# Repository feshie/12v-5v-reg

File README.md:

12v-5v-reg
==========

A switched 12Volt to 5Volt regulator

Will take a nominal 12v in (designed for a lead acid) and produced a regulated 5v supply capable of supplying 2A.

The onboard LEDs show the prescenec of 12V, the switch status, and the prescence of the 5V output.  These LEDs can be disabled to minimise power usage

There is a bypass jumper to enable the output to remain active independently of the enable status.

The enable pins will turn the output on high.

This board has yet to be built and tested so should be considered in alpha status.

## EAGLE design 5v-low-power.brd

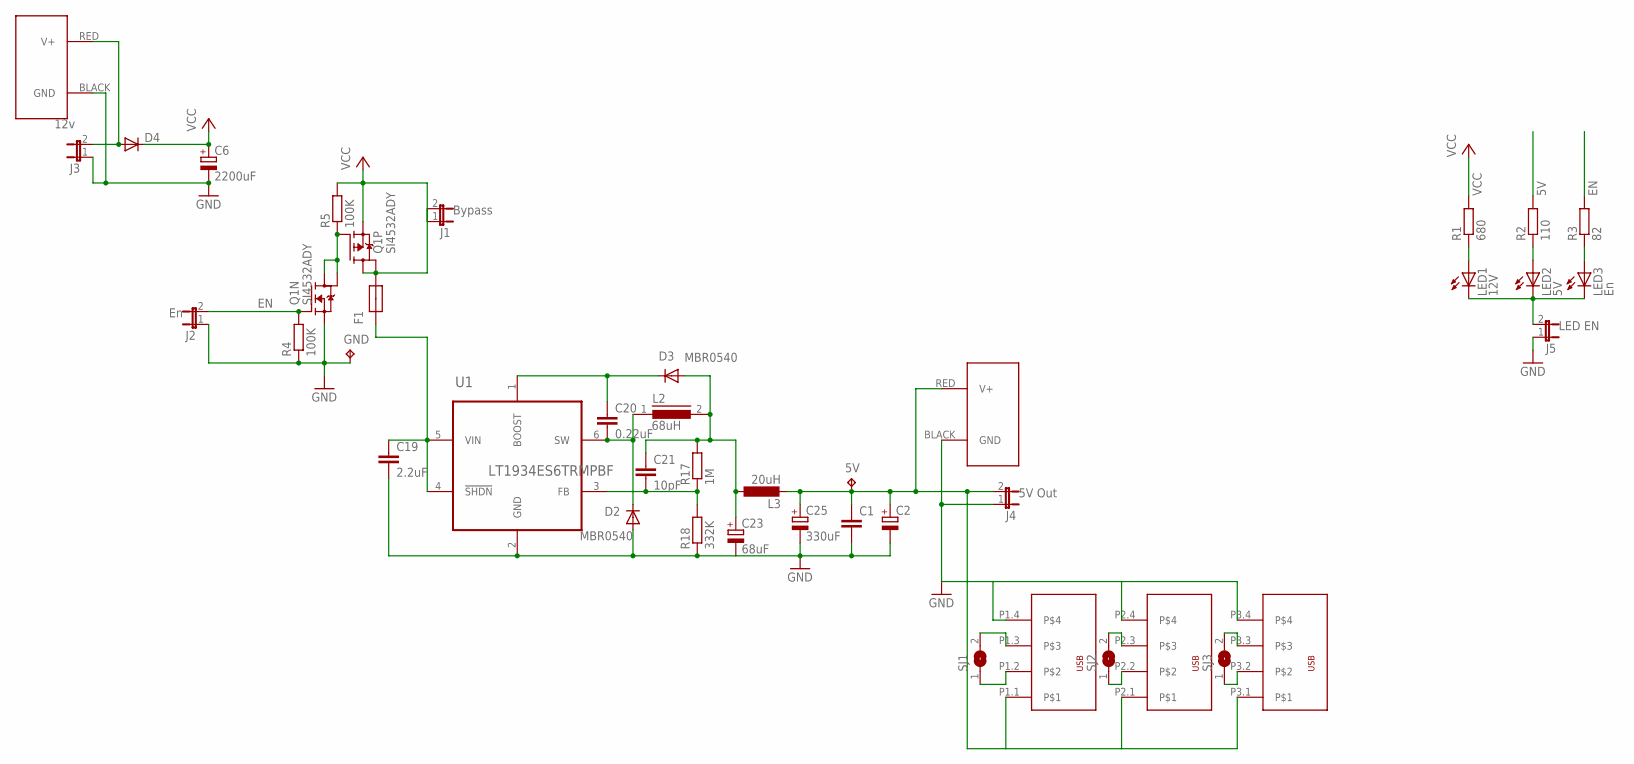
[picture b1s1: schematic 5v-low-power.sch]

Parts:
5V: 5V B; B1,27
C1: C-EUC0805; C0805
C2: CPOL-EUB/3528-21R; B/3528-21R
C6: 2200uF; E5-13
C19: 2.2uF; C0805
C20: 0.22uF; C0805
C21: 10pF; C0805
C23: 68uF; PANASONIC_E
C25: 330uF; E5-8,5
D2, D3: MBR0540; SOD123
D4: DIODE-SMB; SMB
F1: MF-MSMF110; 1812
GND: 5V B; B1,27
J1: Bypass; 2-MOLEX
J2: En; 2-MOLEX
J3: 12v; 2-MOLEX
J4: 5V Out; 2-MOLEX
J5: LED EN; 2-MOLEX
J6, J7: POWERPOLE_POWER25A; POWERPOLE_PAIR_25A
L2: 68uH; DR127
L3: 20uH; 6000-XXXX-RC
LED1: 12V; CHIP-LED0805
LED2: 5V; CHIP-LED0805
LED3: En; CHIP-LED0805
Q1: SI4532ADY; SO8
R1: 680; R0805
R2: 110; R0805
R3: 82; R0805
R4, R5: 100K; R0805
R17: 1M; R0805
R18: 332K; R0805
SJ1, SJ2, SJ3: SJ
U1: LT1934ES6TRMPBF; SOT95P280X100-6N
U$1: USB_DUAL_VERT+HORIZTRIPPLE; USB_DUAL_HORIZ+VERT

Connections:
5V: 5V.TP, C1.1, C2.+, C25.+, J4.2, J6.RED (V+), L3.2, R2.2, U$1.P1.1, U$1.P2.1, U$1.P3.1
EN: J2.2, Q1.2 (G), R3.2, R4.2
GND: C1.2, C2.-, C6.-, C19.2, C23.-, C25.-, D2.A, GND.TP, J2.1, J3.1, J4.1, J5.1, J6.BLACK (GND), J7.BLACK (GND), Q1.1 (S), R4.1, R18.1, U1.2 (GND), U$1.P1.4, U$1.P2.4, U$1.P3.4
LEDGND1: J5.2, LED1.C, LED2.C, LED3.C
unnamed: LED1.A, R1.1
unnamed: SJ1.2, U$1.P1.3
unnamed: D4.A, J3.2, J7.RED (V+)
unnamed: SJ1.1, U$1.P1.2
unnamed: SJ2.1, U$1.P2.2
unnamed: SJ2.2, U$1.P2.3
unnamed: SJ3.2, U$1.P3.3
unnamed: SJ3.1, U$1.P3.2
unnamed: Q1.4 (G), Q1.7 (D), Q1.8 (D), R5.1
unnamed: LED2.A, R2.1
unnamed: LED3.A, R3.1
unnamed: C20.2, D2.C, L2.1, U1.6 (SW)
unnamed: F1.2, J1.2, Q1.5 (D), Q1.6 (D)
unnamed: C21.1, C23.+, D3.A, L2.2, L3.1, R17.2
unnamed: C20.1, D3.C, U1.1 (BOOST)
unnamed: C21.2, R17.1, R18.2, U1.3 (FB)
VCC: C6.+, D4.C, J1.1, Q1.3 (S), R1.2, R5.2
VCC_HP2_SW: C19.1, F1.1, U1.4 (!SHDN), U1.5 (VIN)

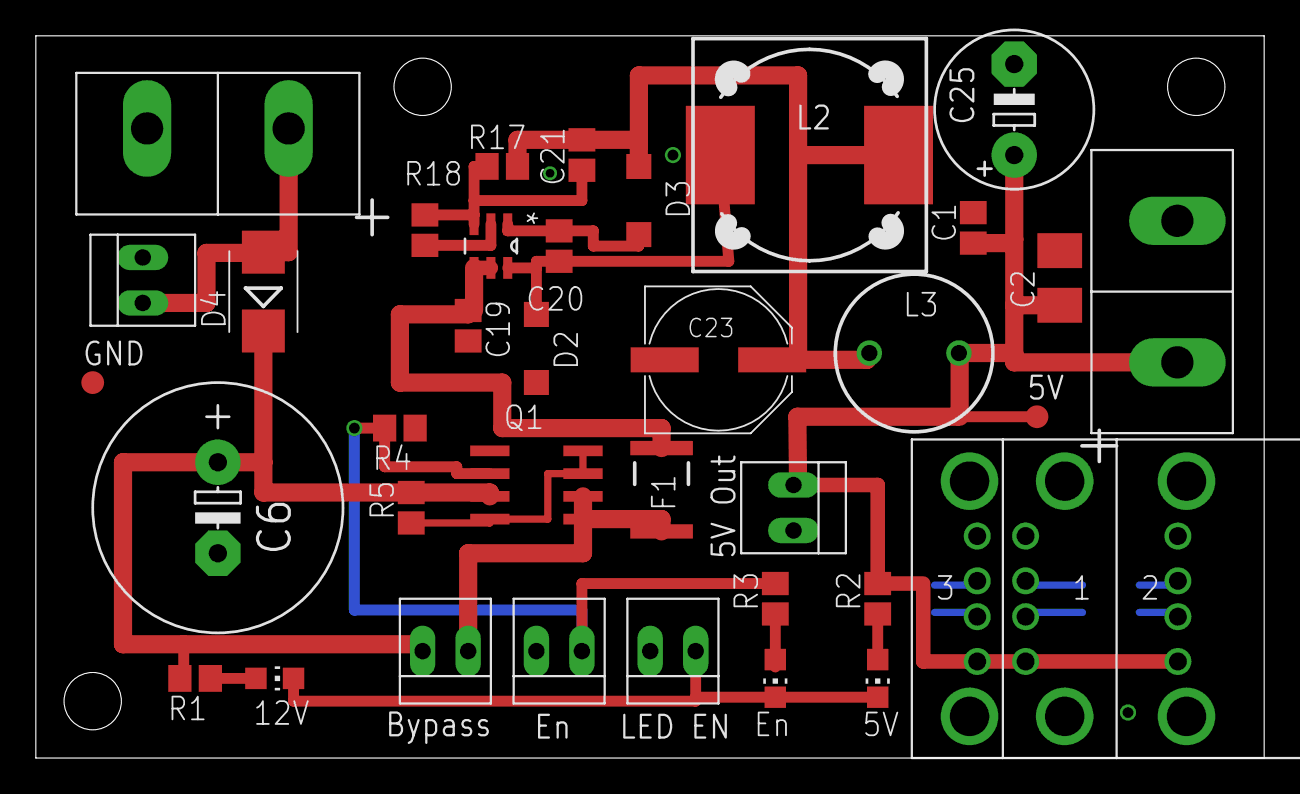
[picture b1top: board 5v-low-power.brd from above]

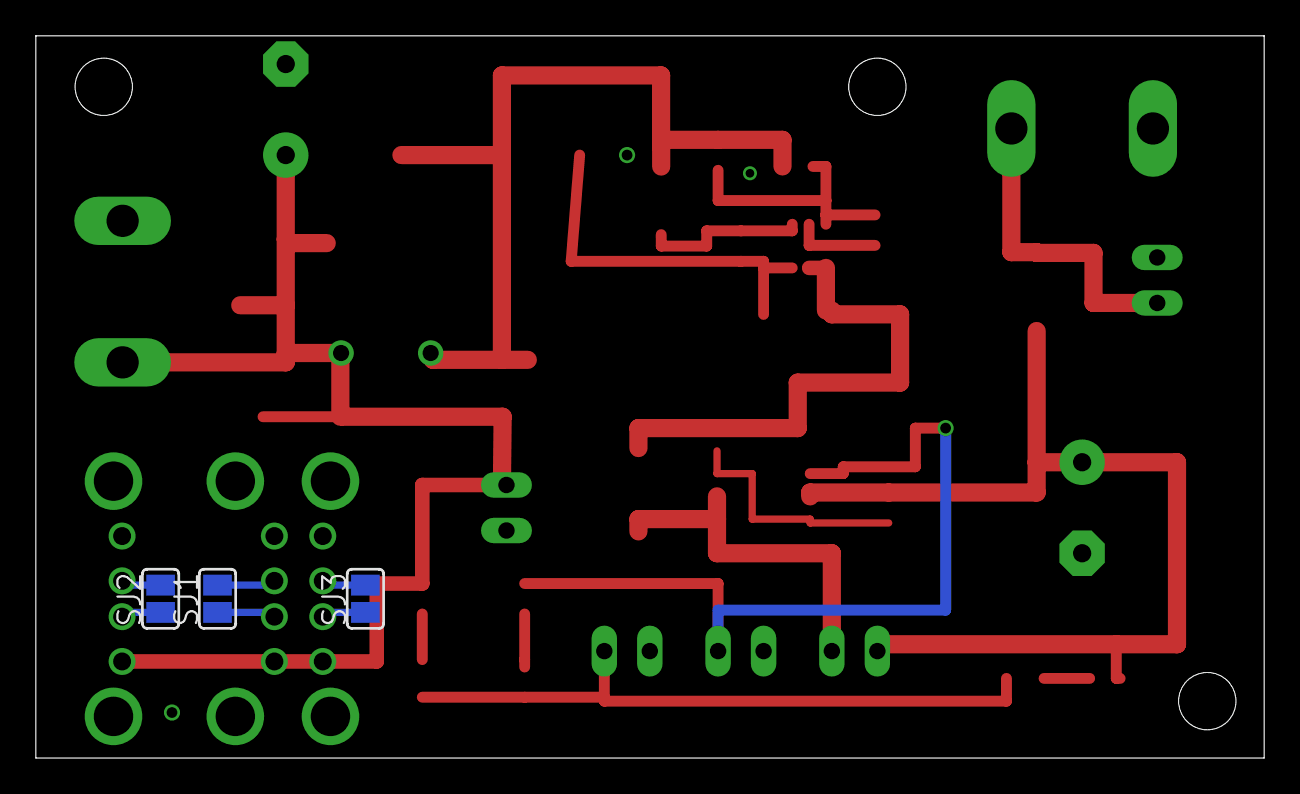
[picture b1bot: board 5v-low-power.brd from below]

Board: 2 copper layers, 68.6 x 40.3 mm, 39 parts (3 on the bottom side), 22 nets.

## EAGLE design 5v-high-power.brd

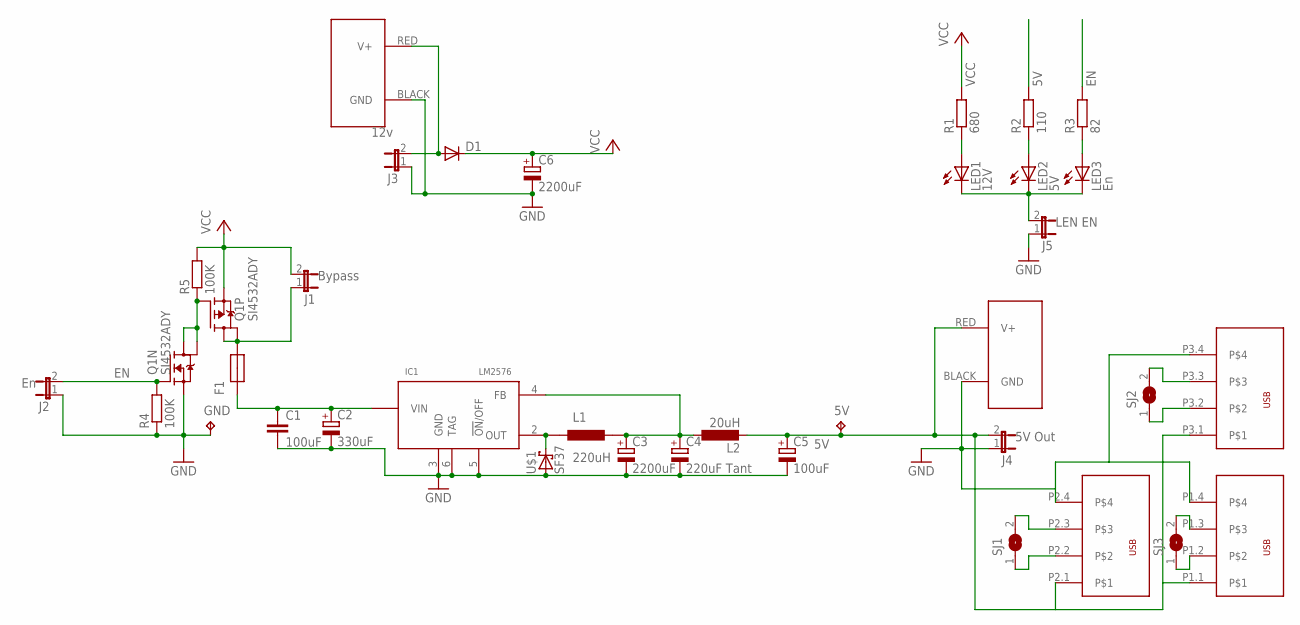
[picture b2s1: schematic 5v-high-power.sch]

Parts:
5V: 5V B; B1,27
C1: 100uF; C1210K
C2: 330uF; E5-8,5
C3, C6: 2200uF; E5-13
C4: 220uF Tant; B/3528-21R
C5: 100uF; PANASONIC_E
D1: DIODE-SMB; SMB
F1: MF-MSMF110; 1812
GND: 5V B; B1,27
IC1: LM2576; TO263
J1: Bypass; 2-MOLEX
J2: En; 2-MOLEX
J3: 12v; 2-MOLEX
J4: 5V Out; 2-MOLEX
J5: LEN EN; 2-MOLEX
J6, J7: POWERPOLE_POWER25A; POWERPOLE_PAIR_25A
L1: 220uH; DR127
L2: 20uH; 6000-XXXX-RC
LED1: 12V; CHIP-LED0805
LED2: 5V; CHIP-LED0805
LED3: En; CHIP-LED0805
Q1: SI4532ADY; SO8
R1: 680; R0805
R2: 110; R0805
R3: 82; R0805
R4, R5: 100K; R0805
SJ1, SJ2, SJ3: SJ
U$1: SF37; DO-201AD
U$2: USB_DUAL_VERT+HORIZTRIPPLE; USB_DUAL_HORIZ+VERT

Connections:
5V: 5V.TP, C5.+, J4.2, J6.RED (V+), L2.2, R2.2, U$2.P1.1, U$2.P2.1, U$2.P3.1
EN: J2.2, Q1.2 (G), R3.2, R4.2
GND: C1.2, C2.-, C3.-, C4.-, C5.-, C6.-, GND.TP, IC1.3 (GND), IC1.5 (!ON!/OFF), IC1.6 (TAG), J2.1, J3.1, J4.1, J5.1, J6.BLACK (GND), J7.BLACK (GND), Q1.1 (S), R4.1, U$1.2 (A), U$2.P1.4, U$2.P2.4, U$2.P3.4
LEDGND: J5.2, LED1.C, LED2.C, LED3.C
unnamed: D1.A, J3.2, J7.RED (V+)
unnamed: LED1.A, R1.1
unnamed: SJ1.2, U$2.P2.3
unnamed: SJ1.1, U$2.P2.2
unnamed: SJ2.2, U$2.P3.3
unnamed: SJ2.1, U$2.P3.2
unnamed: SJ3.2, U$2.P1.3
unnamed: SJ3.1, U$2.P1.2
unnamed: Q1.4 (G), Q1.7 (D), Q1.8 (D), R5.1
unnamed: LED2.A, R2.1
unnamed: LED3.A, R3.1
unnamed: F1.2, J1.1, Q1.5 (D), Q1.6 (D)
unnamed: C3.+, C4.+, IC1.4 (FB), L1.2, L2.1
unnamed: IC1.2 (OUT), L1.1, U$1.1 (C)
VCC: C6.+, D1.C, J1.2, Q1.3 (S), R1.2, R5.2
VCC_HP2_SW: C1.1, C2.+, F1.1, IC1.1 (VIN)

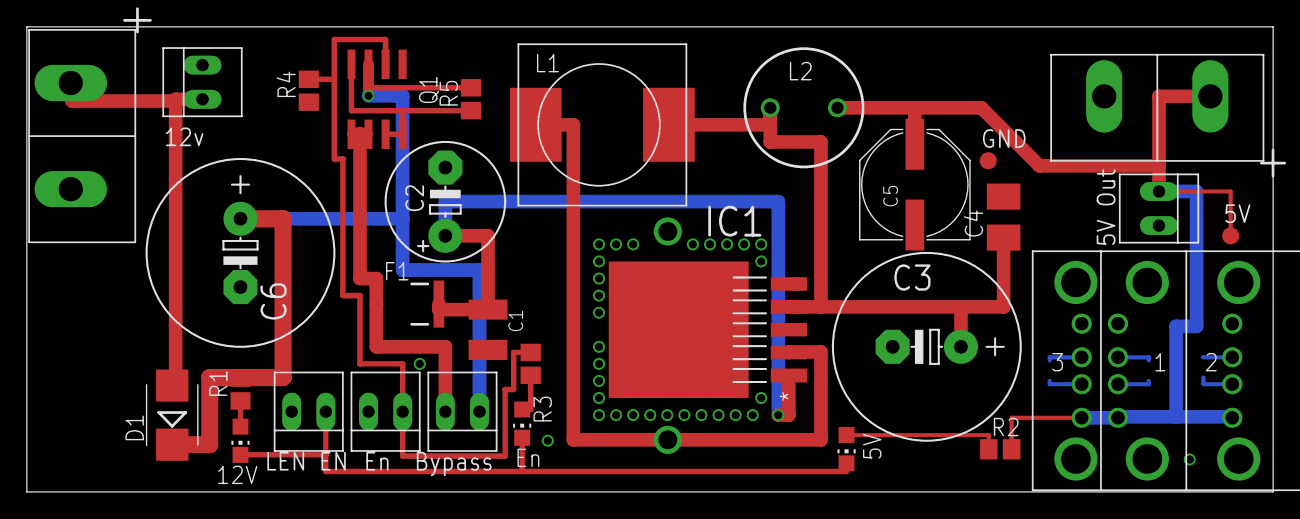
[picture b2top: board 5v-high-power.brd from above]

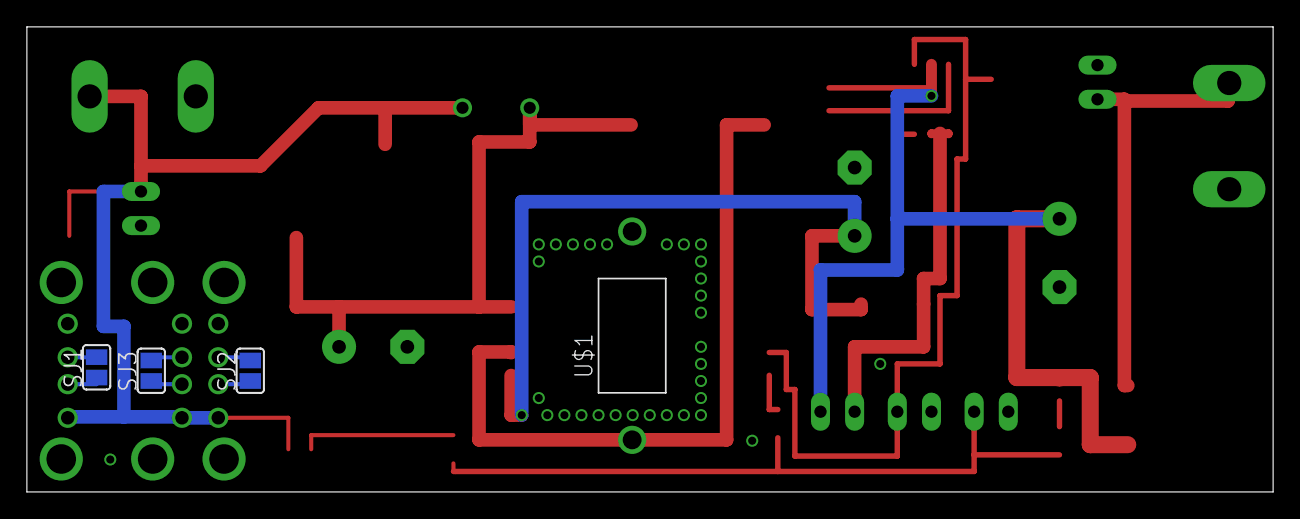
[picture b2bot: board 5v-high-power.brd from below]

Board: 2 copper layers, 92.7 x 34.6 mm, 34 parts (4 on the bottom side), 20 nets.

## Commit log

2014-04-13 First version using molex KK as the power input
2014-04-29 power pole in and out now added
2014-05-02 Existing boards renamed to allow addition of low power
2014-05-02 First version of low power switched board
2014-05-02 changed to correct powerpole version added current rating onto docu layer
2014-05-12 uses a4 frame and smaller ground plane area to make printing better
2014-05-13 Added additional USB footprints and rotated some powerpoles
2014-05-13 moved a couple of components
2014-05-13 minor silk screen tweaks
2014-05-14 bump version number for hackvana regeneration
2014-05-27 cutter changed to 0.15mm
2014-06-05 now uses DR127 footprint for big inductor
2014-06-05 Added more smoothing caps
